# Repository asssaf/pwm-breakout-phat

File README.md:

# pwm-breakout-phat
A pHAT for Raspberry Pi, breaking out the PWM pins and some proto area.

The PWM pins are broken out into four 3-pin connectors that can be used with 5V servos. Granted, it's not recommended to run a servo directly from the pi pins without any protection. 
But in practice, running micro servos (such as sg90), especially one at a time, should be ok (but do it at your own risk). 

In order to enable hardware PWM, the appropriate overlay needs to be enabled in `config.txt`. For example:
```
dtoverlay=pwm-2chan,pin=12,func=4,pin2=13,func2=4
```

The board also has a couple of STEMMA-QT connectors for I2C convenience.

This was my first attempt at designing a PCB in kicad.

## Schematic

## PCB

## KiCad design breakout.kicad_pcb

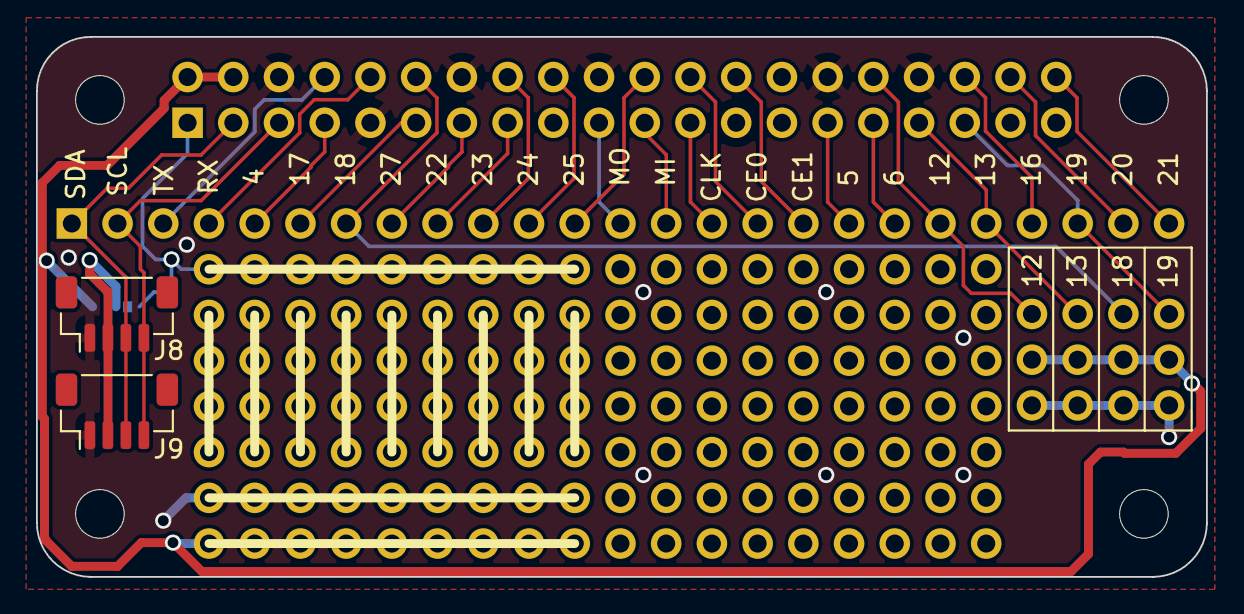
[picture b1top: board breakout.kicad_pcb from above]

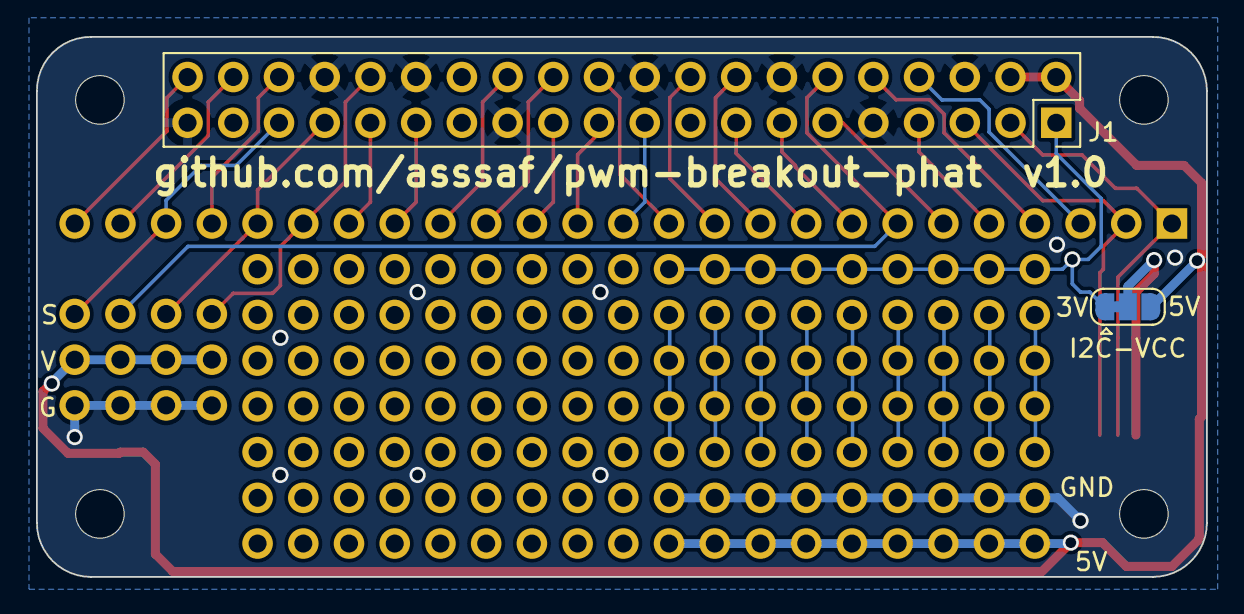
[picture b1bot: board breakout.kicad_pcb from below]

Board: 2 copper layers, 65.0 x 30.0 mm, 22 parts (2 on the bottom side), 29 nets.

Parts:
J1: GPIO; PinSocket_2x20_P2.54mm_Vertical
J2, J3, J4: Conn_01x01; NineConnectedPads
J6: BO; PinSocket_1x25_P2.54mm_Vertical
J8, J9: Conn_01x04_Female; JST_SH_BM04B-SRSS-TB_1x04-1MP_P1.00mm_Vertical
JP2: SolderJumper_3_Bridged12; SolderJumper-3_P1.3mm_Bridged12_RoundedPad1.0x1.5mm
MH1, MH2, MH3, MH4: MountingHole_2.7mm_M2.5
P1, P2, P3, P4, P5, P6, P7, P8, P9: Conn_01x01; ConnectedPads_01x04
U2: FourServos

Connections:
+3V3: J1.1, J1.17, J4.1, JP2.1 (A)
+5V: J1.2, J1.4, J2.1, JP2.3 (B), U2.2 (VCC)
/GPIO[2]/SDA1: J1.3, J6.1 (SDA), J8.3, J9.3
/GPIO[3]/SCL1: J1.5, J6.2 (SCL), J8.4, J9.4
/GPIO[4]/GPCLK0: J1.7, J6.5 (4)
/GPIO[5]: J1.29, J6.18 (5)
/GPIO[6]: J1.31, J6.19 (6)
/GPIO[7]/SPI0.CE1: J1.26, J6.17 (CE1)
/GPIO[8]/SPI0.CE0: J1.24, J6.16 (CE0)
/GPIO[9]/SPI0.MISO: J1.21, J6.14 (MISO)
/GPIO[10]/SPI0.MOSI: J1.19, J6.13 (MOSI)
/GPIO[11]/SPI0.SCLK: J1.23, J6.15 (CLK)
/GPIO[12]/PWM0: J1.32, J6.20 (12), U2.3 (SIG1)
/GPIO[13]/PWM1: J1.33, J6.21 (13), U2.4 (SIG2)
/GPIO[14]/TXD0: J1.8, J6.3 (TX)
/GPIO[15]/RXD0: J1.10, J6.4 (RX)
/GPIO[16]: J1.36, J6.22 (16)
/GPIO[17]: J1.11, J6.6 (17)
/GPIO[18]/PCM.CLK: J1.12, J6.7 (18), U2.5 (SIG3)
/GPIO[19]/PCM.FS: J1.35, J6.23 (19), U2.6 (SIG4)
/GPIO[20]/PCM.DIN: J1.38, J6.24 (20)
/GPIO[21]/PCM.DOUT: J1.40, J6.25 (21)
/GPIO[22]: J1.15, J6.9 (22)
/GPIO[23]: J1.16, J6.10 (23)
/GPIO[24]: J1.18, J6.11 (24)
/GPIO[25]: J1.22, J6.12 (25)
/GPIO[27]: J1.13, J6.8 (27)
/I2CVCC: J8.2, J9.2, JP2.2 (C)
GND: J1.6, J1.9, J1.14, J1.20, J1.25, J1.30, J1.34, J1.39, J3.1, J8.1, J9.1, U2.1 (GND)

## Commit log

2023-11-10 initial
2023-11-10 add url
2023-11-12 add refs for connectors
2023-11-12 add LCSC Part Number
2023-11-12 cleanup
2023-11-24 add assets for readme
2023-11-24 add media in readme
2023-11-24 add schematic in readme
2023-11-24 add dtoverlay example in readme
2023-11-24 add pcb exports from kicad in readme
